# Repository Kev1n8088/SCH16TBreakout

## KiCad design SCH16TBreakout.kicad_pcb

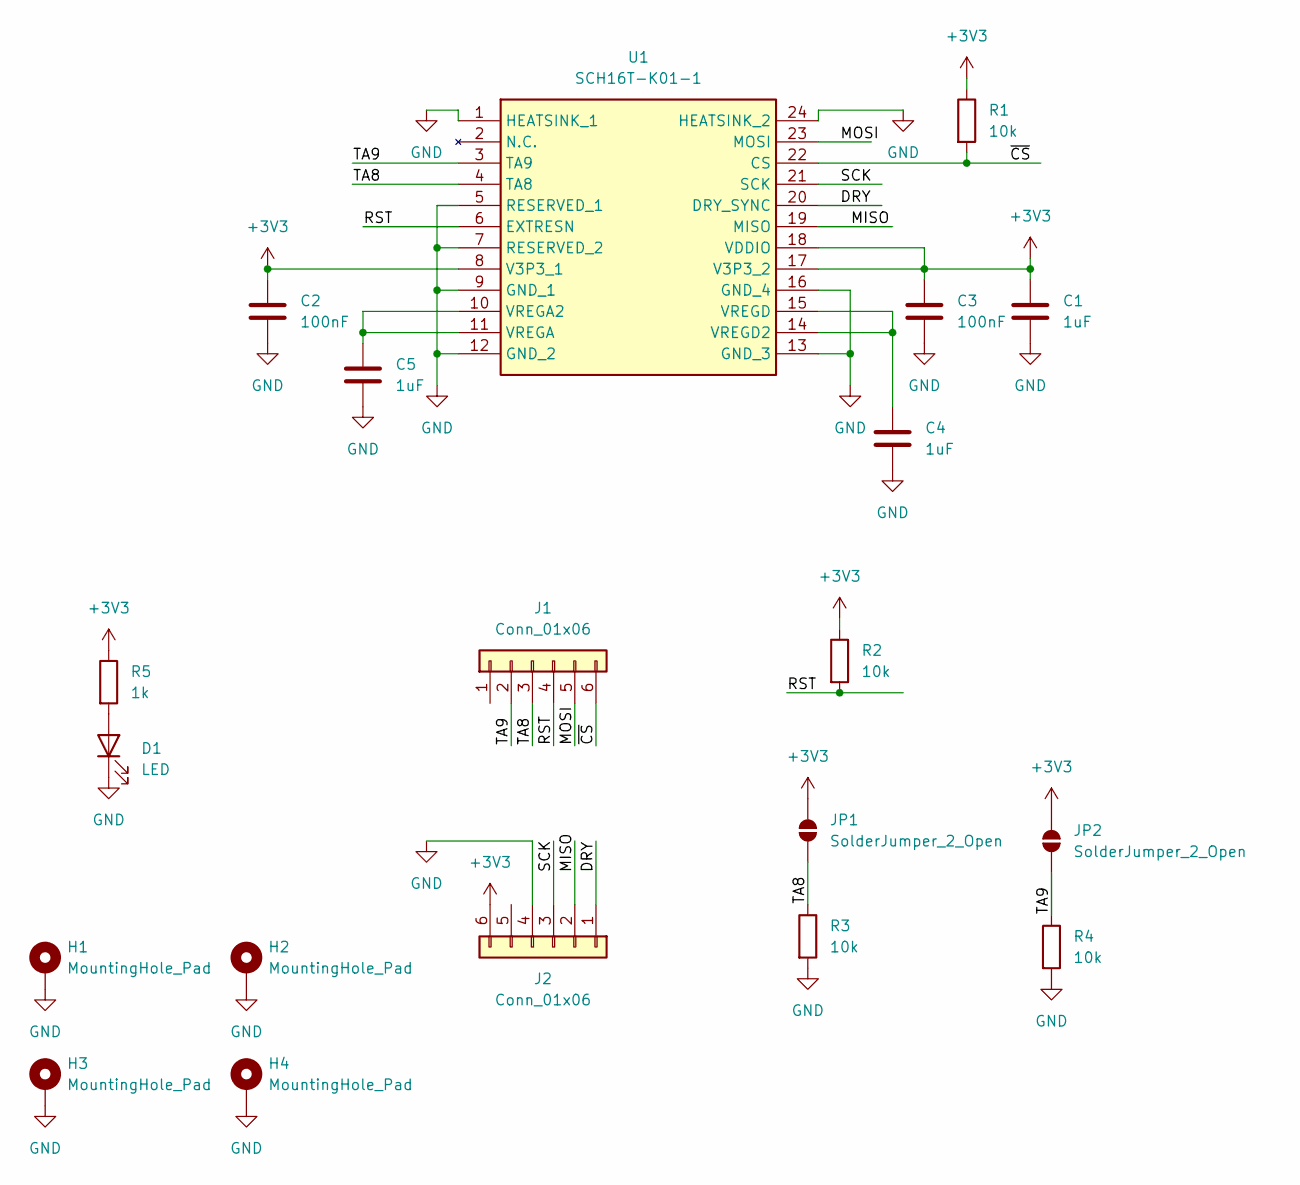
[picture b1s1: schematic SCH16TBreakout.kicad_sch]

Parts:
C1, C4, C5: 1uF; C_0603_1608Metric
C2, C3: 100nF; C_0603_1608Metric
D1: LED; LED_0603_1608Metric
H1, H2, H3, H4: MountingHole_Pad; MountingHole_2.2mm_M2_ISO7380_Pad
J1, J2: Conn_01x06; PinHeader_1x06_P2.54mm_Vertical
JP1, JP2: SolderJumper_2_Open; SolderJumper-2_P1.3mm_Open_TrianglePad1.0x1.5mm
R1, R2, R3, R4: 10k; R_0603_1608Metric
R5: 1k; R_0603_1608Metric
U1: SCH16T-K01-1; SCH16TK011; Mouser Part Number 81-SCH16T-K01-1

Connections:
+3V3: C1.1, C2.1, C3.1, J2.6, JP1.2 (B), JP2.2 (B), R1.1, R2.1, R5.1, U1.8 (V3P3_1), U1.17 (V3P3_2), U1.18 (VDDIO)
/DRY: J2.1, U1.20 (DRY_SYNC)
/MISO: J2.2, U1.19 (MISO)
/MOSI: J1.5, U1.23 (MOSI)
/RST: J1.4, R2.2, U1.6 (EXTRESN)
/SCK: J2.3, U1.21 (SCK)
/TA8: J1.3, JP1.1 (A), R3.1, U1.4 (TA8)
/TA9: J1.2, JP2.1 (A), R4.1, U1.3 (TA9)
/~CS: J1.6, R1.2, U1.22 (CS)
GND: C1.2, C2.2, C3.2, C4.2, C5.2, D1.1 (K), H1.1, H2.1, H3.1, H4.1, J2.4, R3.2, R4.2, U1.1 (HEATSINK_1), U1.5 (RESERVED_1), U1.7 (RESERVED_2), U1.9 (GND_1), U1.12 (GND_2), U1.13 (GND_3), U1.16 (GND_4), U1.24 (HEATSINK_2)
unnamed: D1.2 (A), R5.2
unnamed: C5.1, U1.10 (VREGA2), U1.11 (VREGA)
unnamed: C4.1, U1.14 (VREGD2), U1.15 (VREGD)

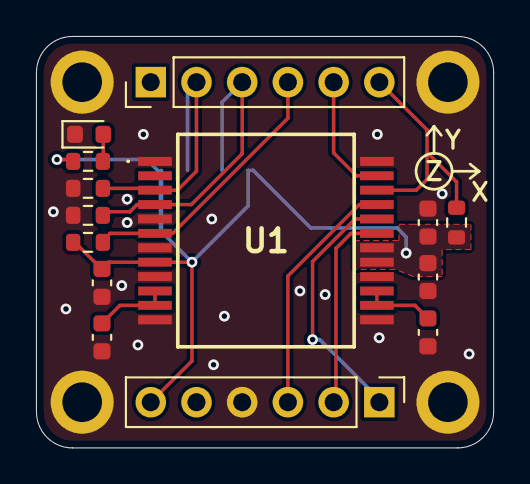
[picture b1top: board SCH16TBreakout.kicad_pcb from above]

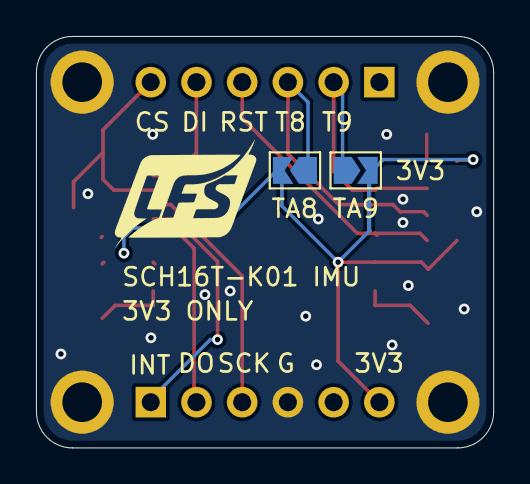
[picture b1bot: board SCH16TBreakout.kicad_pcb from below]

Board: 2 copper layers, 25.4 x 22.9 mm, 20 parts (2 on the bottom side), 13 nets.

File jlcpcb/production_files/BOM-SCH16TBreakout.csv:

Comment,Designator,Footprint,LCSC,Quantity
100nF,"C2,C3",C_0603_1608Metric,C14663,2
1uF,"C1,C4,C5",C_0603_1608Metric,C15849,3
1k,R5,R_0603_1608Metric,C21190,1
LED,D1,LED_0603_1608Metric,C2286,1
10k,"R1,R2,R3,R4",R_0603_1608Metric,C25804,4
SCH16T-K01-1,U1,SCH16TK011,C27618127,1

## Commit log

2025-06-26 v1.0 finalized
